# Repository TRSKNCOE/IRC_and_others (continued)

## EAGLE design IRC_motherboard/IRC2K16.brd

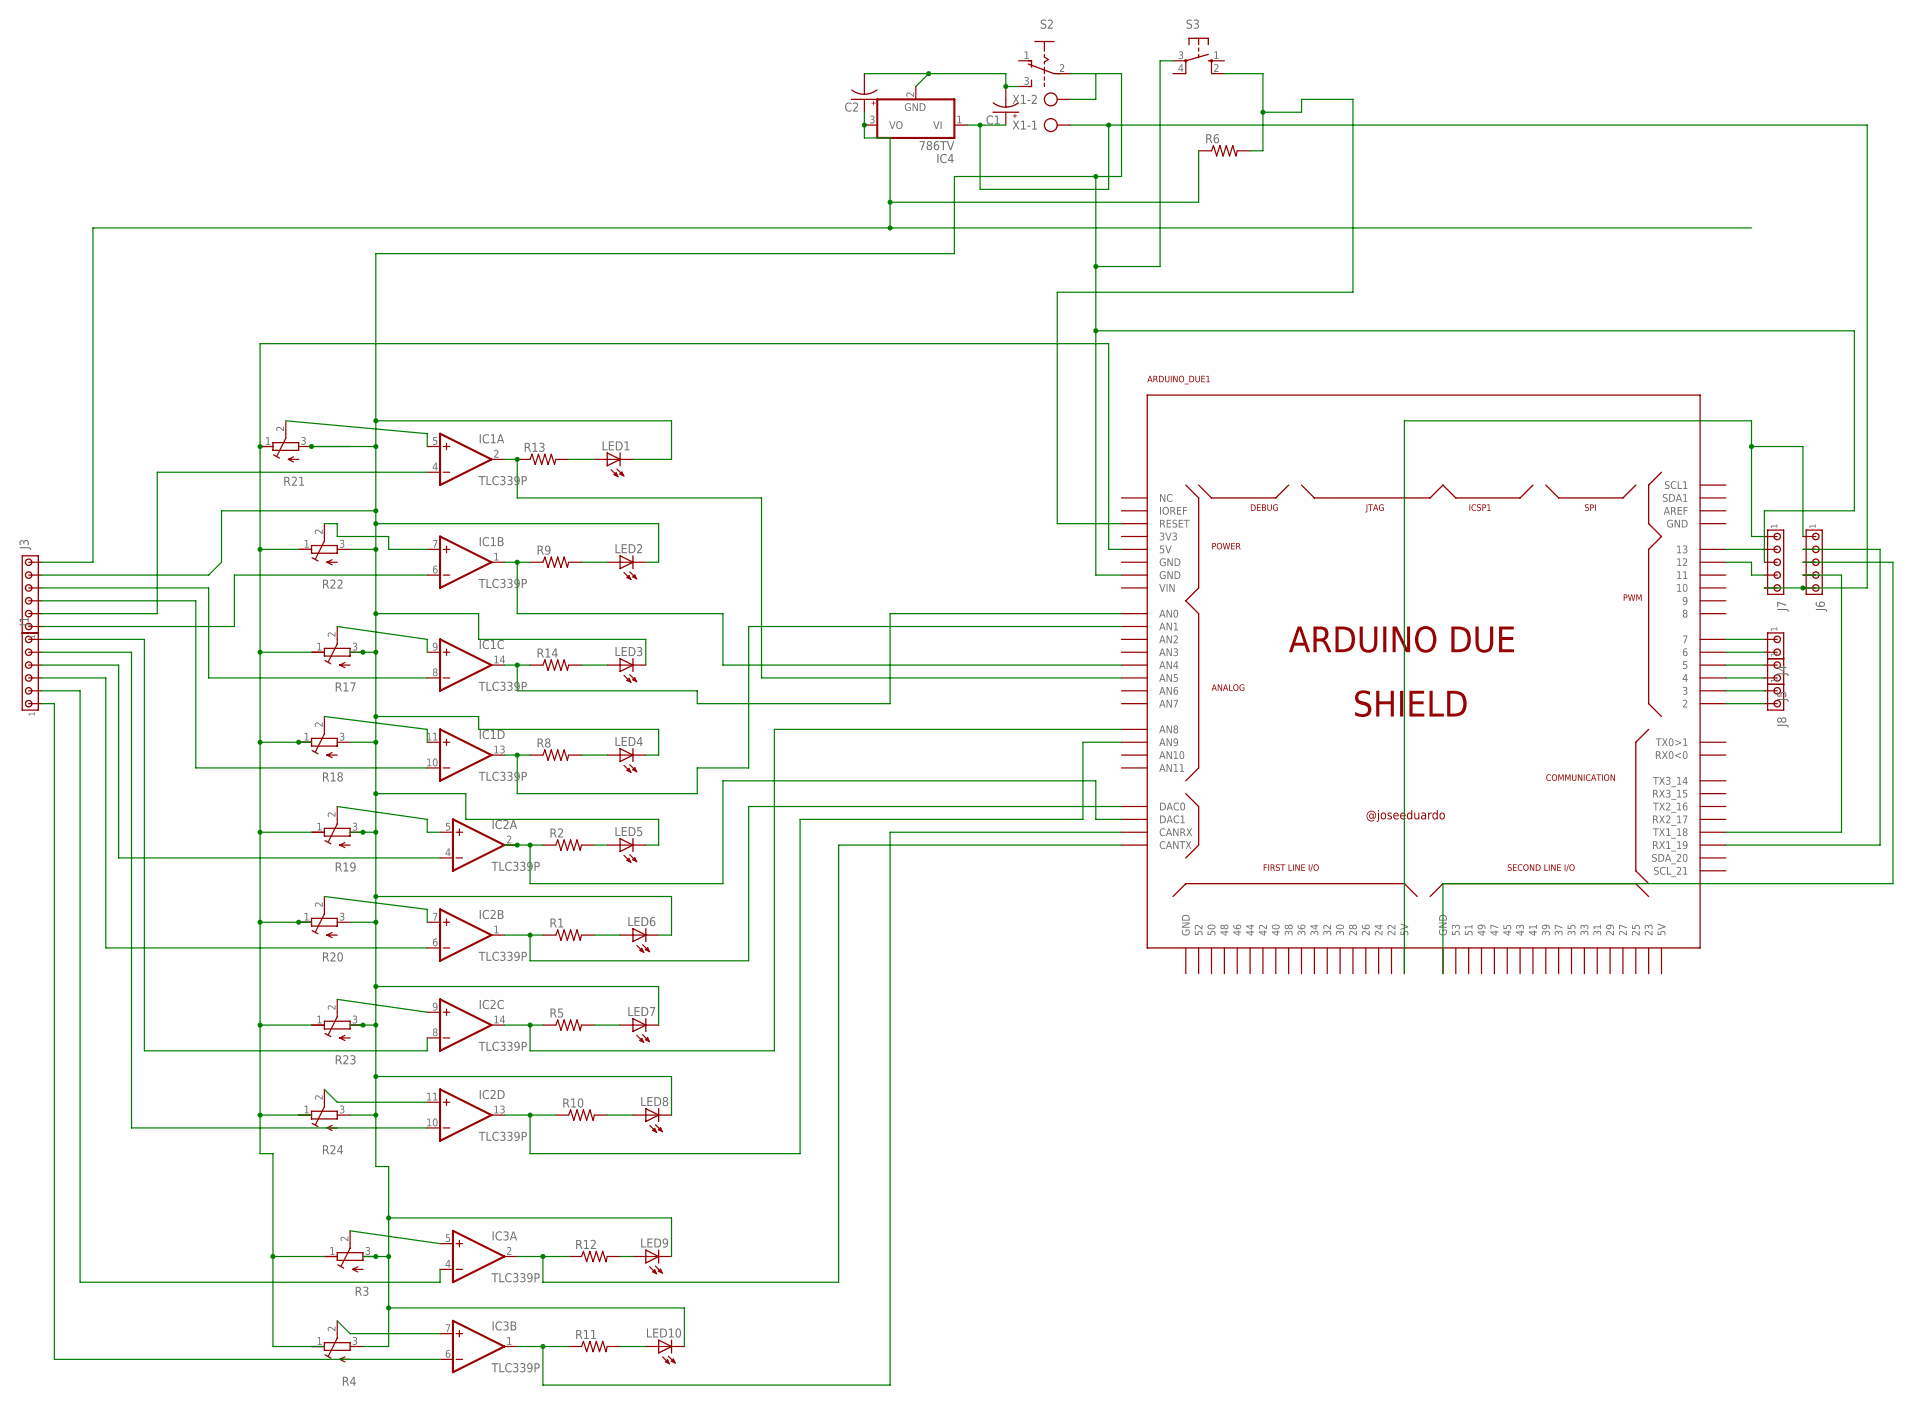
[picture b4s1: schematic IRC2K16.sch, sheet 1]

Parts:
ARDUINO_DUE1: ARDUINO_DUE_SHIELD
C1, C2: CPOL-USE5-10.5; E5-10,5
IC1, IC2, IC3: TLC339P; DIL14
IC4: 786TV; TO220V
J1, J3: MTA06-100; 10X06MTA
J4, J5, J8: MTA02-100; 10X02MTA
J6, J7: MTA05-100; 10X05MTA
LED1, LED2, LED3, LED4, LED5, LED6, LED7, LED8, LED9, LED10: LED3MM
R1, R2, R5, R8, R9, R10, R11, R12, R13, R14: R-US_0411/3V; 0411V
R3, R4, R17, R18, R19, R20, R21, R22, R23, R24: R-TRIMMT93YA; RTRIMT93YA
R6: R-US_0207/10; 0207/10
S2: A68-A31
S3: 10-XX; B3F-10XX
X1: AK300/2

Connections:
unnamed: ARDUINO_DUE1.7, J4.1
unnamed: IC1.4 (-IN), J3.5 (2)
unnamed: ARDUINO_DUE1.6, J4.2
unnamed: IC1.6 (-IN), J3.6 (1)
unnamed: IC1.7 (+IN), R22.2 (S)
unnamed: IC1.5 (+IN), R21.2 (S)
unnamed: IC1.9 (+IN), R17.2 (S)
unnamed: IC1.11 (+IN), R18.2 (S)
unnamed: IC2.5 (+IN), R19.2 (S)
unnamed: IC2.7 (+IN), R20.2 (S)
unnamed: IC2.9 (+IN), R23.2 (S)
unnamed: IC2.11 (+IN), R24.2 (S)
unnamed: ARDUINO_DUE1.A5 (AN5), IC1.2 (OUT), R13.1
unnamed: LED1.A, R13.2
unnamed: ARDUINO_DUE1.A4 (AN4), IC1.1 (OUT), R9.1
unnamed: LED2.A, R9.2
unnamed: ARDUINO_DUE1.A0 (AN0), IC1.14 (OUT), R14.1
unnamed: LED3.A, R14.2
unnamed: ARDUINO_DUE1.A1 (AN1), IC1.13 (OUT), R8.1
unnamed: ARDUINO_DUE1.DAC1, IC2.2 (OUT), R2.1
unnamed: ARDUINO_DUE1.DAC0, IC2.1 (OUT), R1.1
unnamed: ARDUINO_DUE1.A8 (AN8), IC2.14 (OUT), R5.1
unnamed: LED4.A, R8.2
unnamed: LED5.A, R2.2
unnamed: LED6.A, R1.2
unnamed: LED7.A, R5.2
unnamed: ARDUINO_DUE1.A9 (AN9), IC2.13 (OUT), R10.1
unnamed: LED8.A, R10.2
unnamed: IC1.8 (-IN), J3.3 (4)
unnamed: ARDUINO_DUE1.5, J5.1
unnamed: IC1.10 (-IN), J3.4 (3)
unnamed: IC2.4 (-IN), J1.3 (4)
unnamed: IC2.6 (-IN), J1.4 (3)
unnamed: IC2.8 (-IN), J1.1 (6)
unnamed: ARDUINO_DUE1.4, J5.2
unnamed: ARDUINO_DUE1.3, J8.1
unnamed: ARDUINO_DUE1.2, J8.2
unnamed: IC2.10 (-IN), J1.2 (5)
unnamed: C1.+, IC4.1 (VI), J6.5, J7.5, X1.1
unnamed: IC3.5 (+IN), R3.2 (S)
unnamed: ARDUINO_DUE1.18 (TX1_18), J6.4
unnamed: IC3.7 (+IN), R4.2 (S)
unnamed: ARDUINO_DUE1.CANTX, IC3.2 (OUT), R12.1
unnamed: LED9.A, R12.2
unnamed: ARDUINO_DUE1.CANRX, IC3.1 (OUT), R11.1
unnamed: LED10.A, R11.2
unnamed: IC3.4 (-IN), J1.5 (2)
unnamed: IC3.6 (-IN), J1.6 (1)
unnamed: C2.+, IC4.3 (VO), J3.1 (6), R6.1
unnamed: ARDUINO_DUE1.13, J7.2
unnamed: ARDUINO_DUE1.RESET, R6.2, S3.2 (S1)
unnamed: C1.-, C2.-, IC4.2 (GND), S2.3 (S)
unnamed: ARDUINO_DUE1.5V0 (5V), IC1.3 (V+), IC2.3 (V+), IC3.3 (V+), R3.1 (A), R4.1 (A), R17.1 (A), R18.1 (A), R19.1 (A), R20.1 (A), R21.1 (A), R22.1 (A), R23.1 (A), R24.1 (A)
unnamed: ARDUINO_DUE1.5V0_1 (5V), J6.1, J7.1
unnamed: ARDUINO_DUE1.12, J7.4
unnamed: ARDUINO_DUE1.19 (RX1_19), J6.2
unnamed: ARDUINO_DUE1.GND_3 (GND), J6.3
unnamed: ARDUINO_DUE1.GND_1 (GND), J3.2 (5), J7.3, LED1.K (C), LED2.K (C), LED3.K (C), LED4.K (C), LED5.K (C), LED6.K (C), LED7.K (C), LED8.K (C), LED9.K (C), LED10.K (C), R3.3 (E), R4.3 (E), R17.3 (E), R18.3 (E), R19.3 (E), R20.3 (E), R21.3 (E), R22.3 (E), R23.3 (E), R24.3 (E), S2.2, S3.3, X1.2
V-: IC1.12 (V-), IC2.12 (V-), IC3.12 (V-)

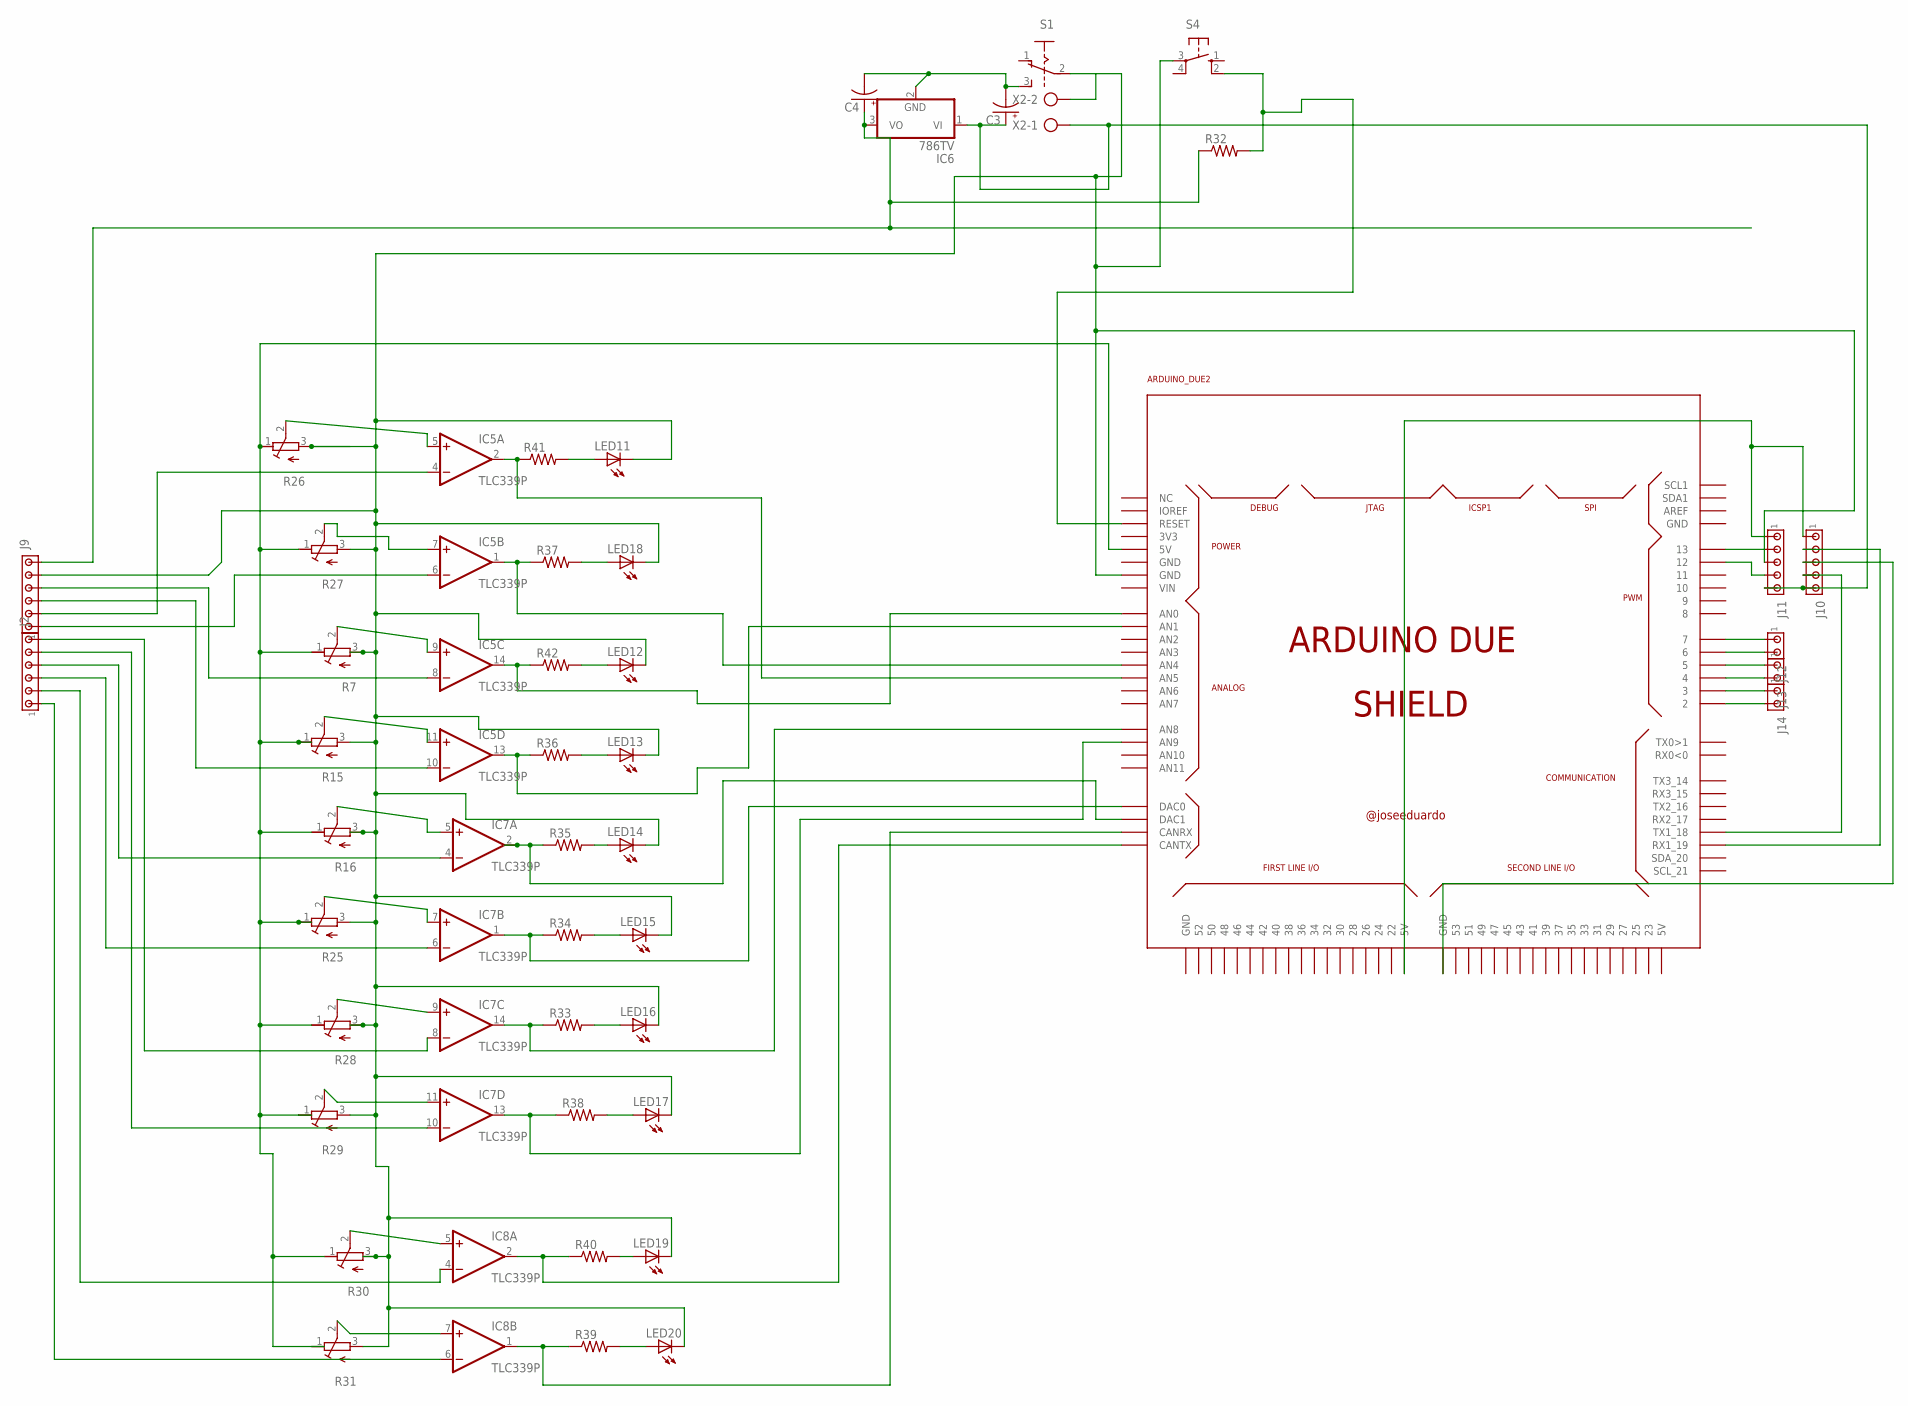
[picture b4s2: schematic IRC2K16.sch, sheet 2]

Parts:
ARDUINO_DUE2: ARDUINO_DUE_SHIELD
C3, C4: CPOL-USE5-10.5; E5-10,5
IC5, IC7, IC8: TLC339P; DIL14
IC6: 786TV; TO220V
J2, J9: MTA06-100; 10X06MTA
J10, J11: MTA05-100; 10X05MTA
J12, J13, J14: MTA02-100; 10X02MTA
LED11, LED12, LED13, LED14, LED15, LED16, LED17, LED18, LED19, LED20: LED3MM
R7, R15, R16, R25, R26, R27, R28, R29, R30, R31: R-TRIMMT93YA; RTRIMT93YA
R32: R-US_0207/10; 0207/10
R33, R34, R35, R36, R37, R38, R39, R40, R41, R42: R-US_0411/3V; 0411V
S1: A68-A31
S4: 10-XX; B3F-10XX
X2: AK300/2

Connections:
unnamed: IC5.7 (+IN), R27.2 (S)
unnamed: IC5.5 (+IN), R26.2 (S)
unnamed: IC5.9 (+IN), R7.2 (S)
unnamed: IC5.11 (+IN), R15.2 (S)
unnamed: IC7.5 (+IN), R16.2 (S)
unnamed: IC7.7 (+IN), R25.2 (S)
unnamed: IC7.9 (+IN), R28.2 (S)
unnamed: IC7.11 (+IN), R29.2 (S)
unnamed: ARDUINO_DUE2.A5 (AN5), IC5.2 (OUT), R41.1
unnamed: ARDUINO_DUE2.A4 (AN4), IC5.1 (OUT), R37.1
unnamed: ARDUINO_DUE2.A0 (AN0), IC5.14 (OUT), R42.1
unnamed: LED12.A, R42.2
unnamed: ARDUINO_DUE2.A1 (AN1), IC5.13 (OUT), R36.1
unnamed: ARDUINO_DUE2.DAC1, IC7.2 (OUT), R35.1
unnamed: ARDUINO_DUE2.DAC0, IC7.1 (OUT), R34.1
unnamed: ARDUINO_DUE2.A8 (AN8), IC7.14 (OUT), R33.1
unnamed: LED13.A, R36.2
unnamed: LED14.A, R35.2
unnamed: LED15.A, R34.2
unnamed: LED16.A, R33.2
unnamed: ARDUINO_DUE2.A9 (AN9), IC7.13 (OUT), R38.1
unnamed: LED17.A, R38.2
unnamed: LED11.A, R41.2
unnamed: LED18.A, R37.2
unnamed: IC5.4 (-IN), J9.5 (2)
unnamed: IC5.6 (-IN), J9.6 (1)
unnamed: IC5.10 (-IN), J9.4 (3)
unnamed: IC7.8 (-IN), J2.1 (6)
unnamed: IC7.10 (-IN), J2.2 (5)
unnamed: ARDUINO_DUE2.7, J12.1
unnamed: ARDUINO_DUE2.6, J12.2
unnamed: ARDUINO_DUE2.5, J13.1
unnamed: ARDUINO_DUE2.4, J13.2
unnamed: ARDUINO_DUE2.3, J14.1
unnamed: ARDUINO_DUE2.2, J14.2
unnamed: C3.+, IC6.1 (VI), J10.5, J11.5, X2.1
unnamed: IC8.5 (+IN), R30.2 (S)
unnamed: IC8.7 (+IN), R31.2 (S)
unnamed: ARDUINO_DUE2.CANTX, IC8.2 (OUT), R40.1
unnamed: LED19.A, R40.2
unnamed: ARDUINO_DUE2.CANRX, IC8.1 (OUT), R39.1
unnamed: LED20.A, R39.2
unnamed: IC8.4 (-IN), J2.5 (2)
unnamed: IC8.6 (-IN), J2.6 (1)
unnamed: C4.+, IC6.3 (VO), J9.1 (6), R32.1
unnamed: ARDUINO_DUE2.RESET, R32.2, S4.2 (S1)
unnamed: IC7.6 (-IN), J2.4 (3)
unnamed: IC7.4 (-IN), J2.3 (4)
unnamed: IC5.8 (-IN), J9.3 (4)
unnamed: C3.-, C4.-, IC6.2 (GND), S1.3 (S)
unnamed: ARDUINO_DUE2.GND_1 (GND), J9.2 (5), J11.3, LED11.K (C), LED12.K (C), LED13.K (C), LED14.K (C), LED15.K (C), LED16.K (C), LED17.K (C), LED18.K (C), LED19.K (C), LED20.K (C), R7.3 (E), R15.3 (E), R16.3 (E), R25.3 (E), R26.3 (E), R27.3 (E), R28.3 (E), R29.3 (E), R30.3 (E), R31.3 (E), S1.2, S4.3, X2.2
unnamed: ARDUINO_DUE2.5V0 (5V), IC5.3 (V+), IC7.3 (V+), IC8.3 (V+), R7.1 (A), R15.1 (A), R16.1 (A), R25.1 (A), R26.1 (A), R27.1 (A), R28.1 (A), R29.1 (A), R30.1 (A), R31.1 (A)
unnamed: ARDUINO_DUE2.5V0_1 (5V), J10.1, J11.1
unnamed: ARDUINO_DUE2.13, J11.2
unnamed: ARDUINO_DUE2.12, J11.4
unnamed: ARDUINO_DUE2.18 (TX1_18), J10.4
unnamed: ARDUINO_DUE2.19 (RX1_19), J10.2
unnamed: ARDUINO_DUE2.GND_3 (GND), J10.3
V-1: IC5.12 (V-), IC7.12 (V-), IC8.12 (V-)

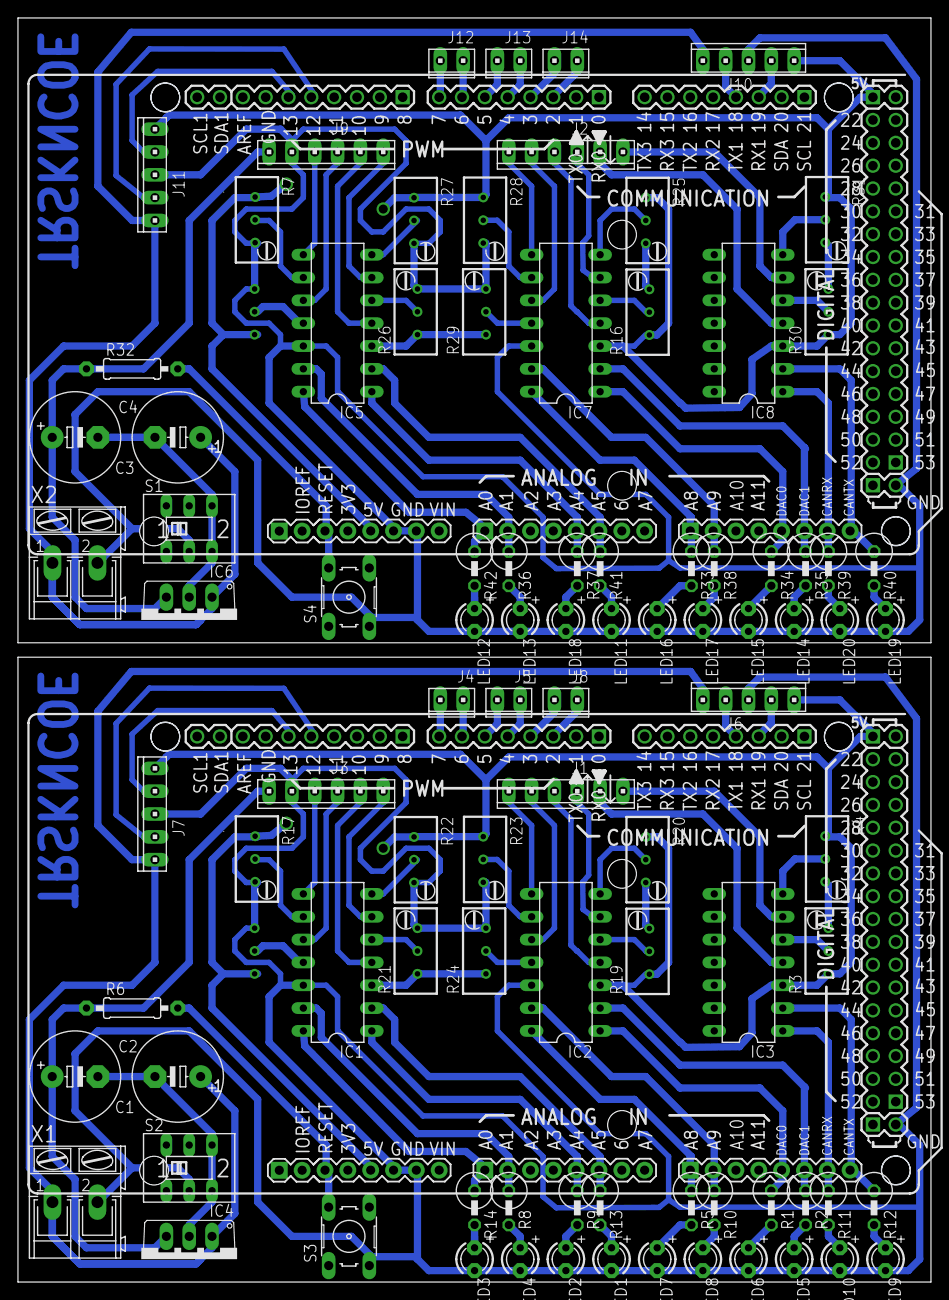
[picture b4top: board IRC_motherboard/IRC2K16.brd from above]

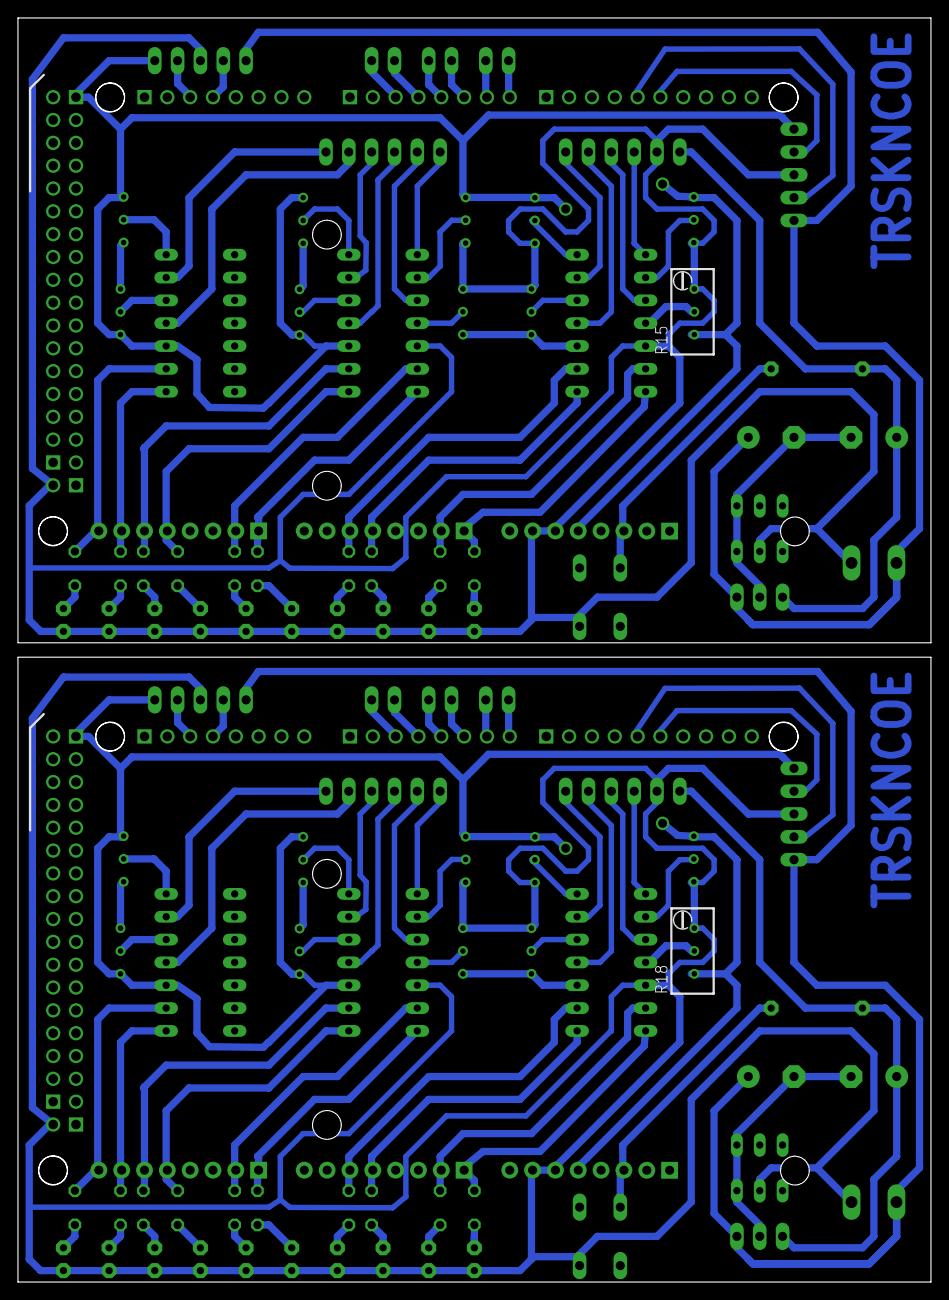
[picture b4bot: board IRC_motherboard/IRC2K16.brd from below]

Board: 2 copper layers, 101.6 x 140.6 mm, 96 parts (2 on the bottom side), 118 nets.

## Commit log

2023-09-15 IRC hardware boards 2016
